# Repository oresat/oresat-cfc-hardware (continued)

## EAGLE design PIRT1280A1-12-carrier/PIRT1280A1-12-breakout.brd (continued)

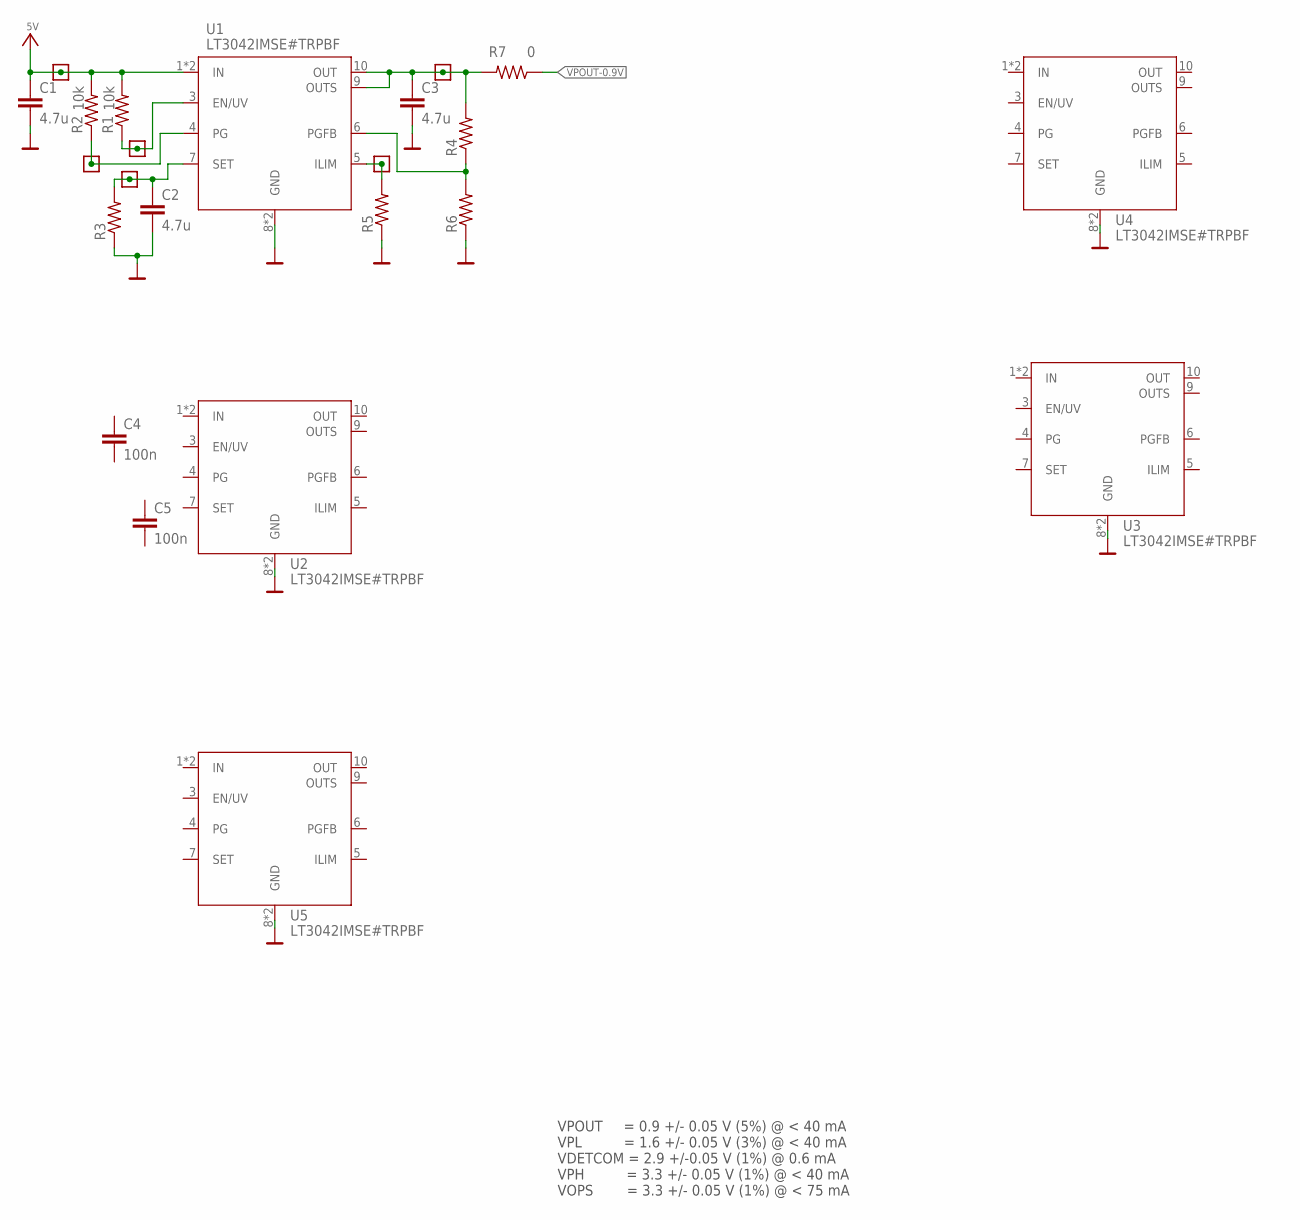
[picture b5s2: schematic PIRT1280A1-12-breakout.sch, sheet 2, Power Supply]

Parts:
C1, C2, C3: 4.7u; .0603-C-NOSILK
C4, C5: 100n; .0603-C-NOSILK
R1, R2: 10k; .0603-C-NOSILK
R3, R4, R5, R6: R-US_0603-C-NOSILK; .0603-C-NOSILK
R7: 0; .0603-C-NOSILK
TP1, TP10, TP11, TP12, TP13, TP14: TEST-POINT-LARGE-SQUARE; 1X01
U1, U2, U3, U4, U5: LT3042IMSE#TRPBF; SOP50P490X110-11N

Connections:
5V: C1.1, R1.2, R2.2, TP12.1, U1.1 (IN), U1.2 (IN)
GND: C1.2, C2.2, C3.2, R3.1, R5.1, R6.1, U1.8 (GND), U1.11 (GND), U2.8 (GND), U2.11 (GND), U3.8 (GND), U3.11 (GND), U4.8 (GND), U4.11 (GND), U5.8 (GND), U5.11 (GND); also elsewhere on the board
IN: U2.1 (IN), U2.2 (IN), U3.1 (IN), U3.2 (IN), U4.1 (IN), U4.2 (IN), U5.1 (IN), U5.2 (IN)
unnamed: R1.1, TP11.1, U1.3 (EN/UV)
unnamed: C2.1, R3.2, TP1.1, U1.7 (SET)
unnamed: R2.1, TP10.1, U1.4 (PG)
unnamed: R5.2, TP14.1, U1.5 (ILIM)
unnamed: R4.1, R6.2, U1.6 (PGFB)
OUT: U2.10 (OUT), U3.10 (OUT), U4.10 (OUT), U5.10 (OUT)
OUTS: U2.9 (OUTS), U3.9 (OUTS), U4.9 (OUTS), U5.9 (OUTS)
VPOUT: C3.1, R4.2, R7.2, TP13.1, U1.9 (OUTS), U1.10 (OUT)
VPOUT-0.9V: R7.1; also elsewhere on the board

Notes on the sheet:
VPOUT = 0.9 +/- 0.05 V (5%) @ < 40 mA VPL = 1.6 +/- 0.05 V (3%) @ < 40 mA VDETCOM = 2.9 +/-0.05 V (1%) @ 0.6 mA VPH = 3.3 +/- 0.05 V (1%) @ < 40 mA VOPS = 3.3 +/- 0.05 V (1%) @ < 75 mA

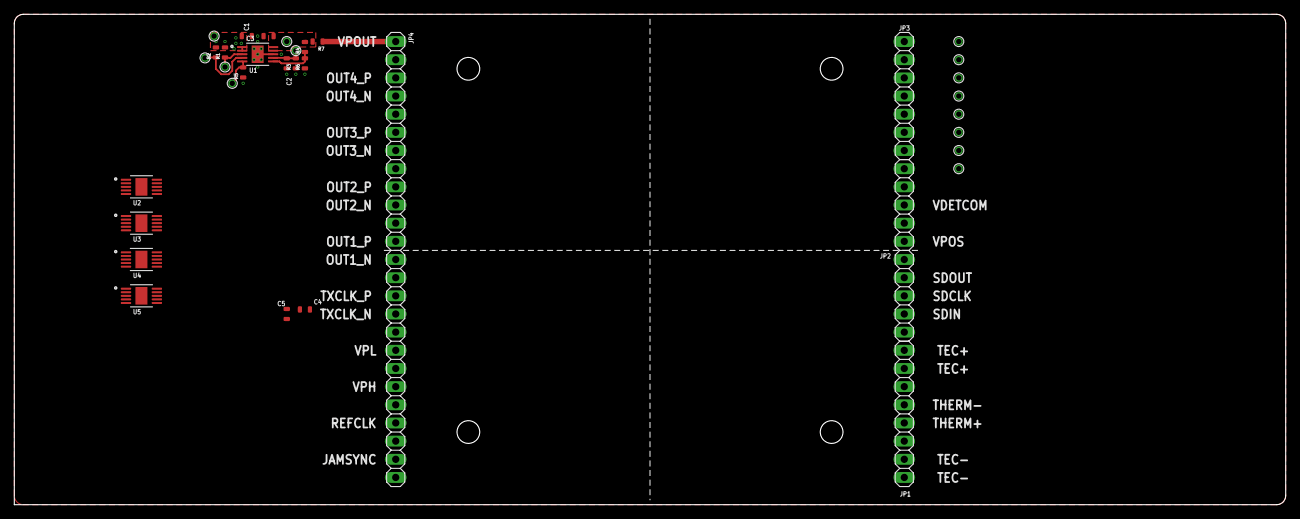
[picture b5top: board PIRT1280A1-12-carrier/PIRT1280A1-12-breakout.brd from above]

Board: 4 copper layers, 177.8 x 68.6 mm, 35 parts (0 on the bottom side), 22 nets.

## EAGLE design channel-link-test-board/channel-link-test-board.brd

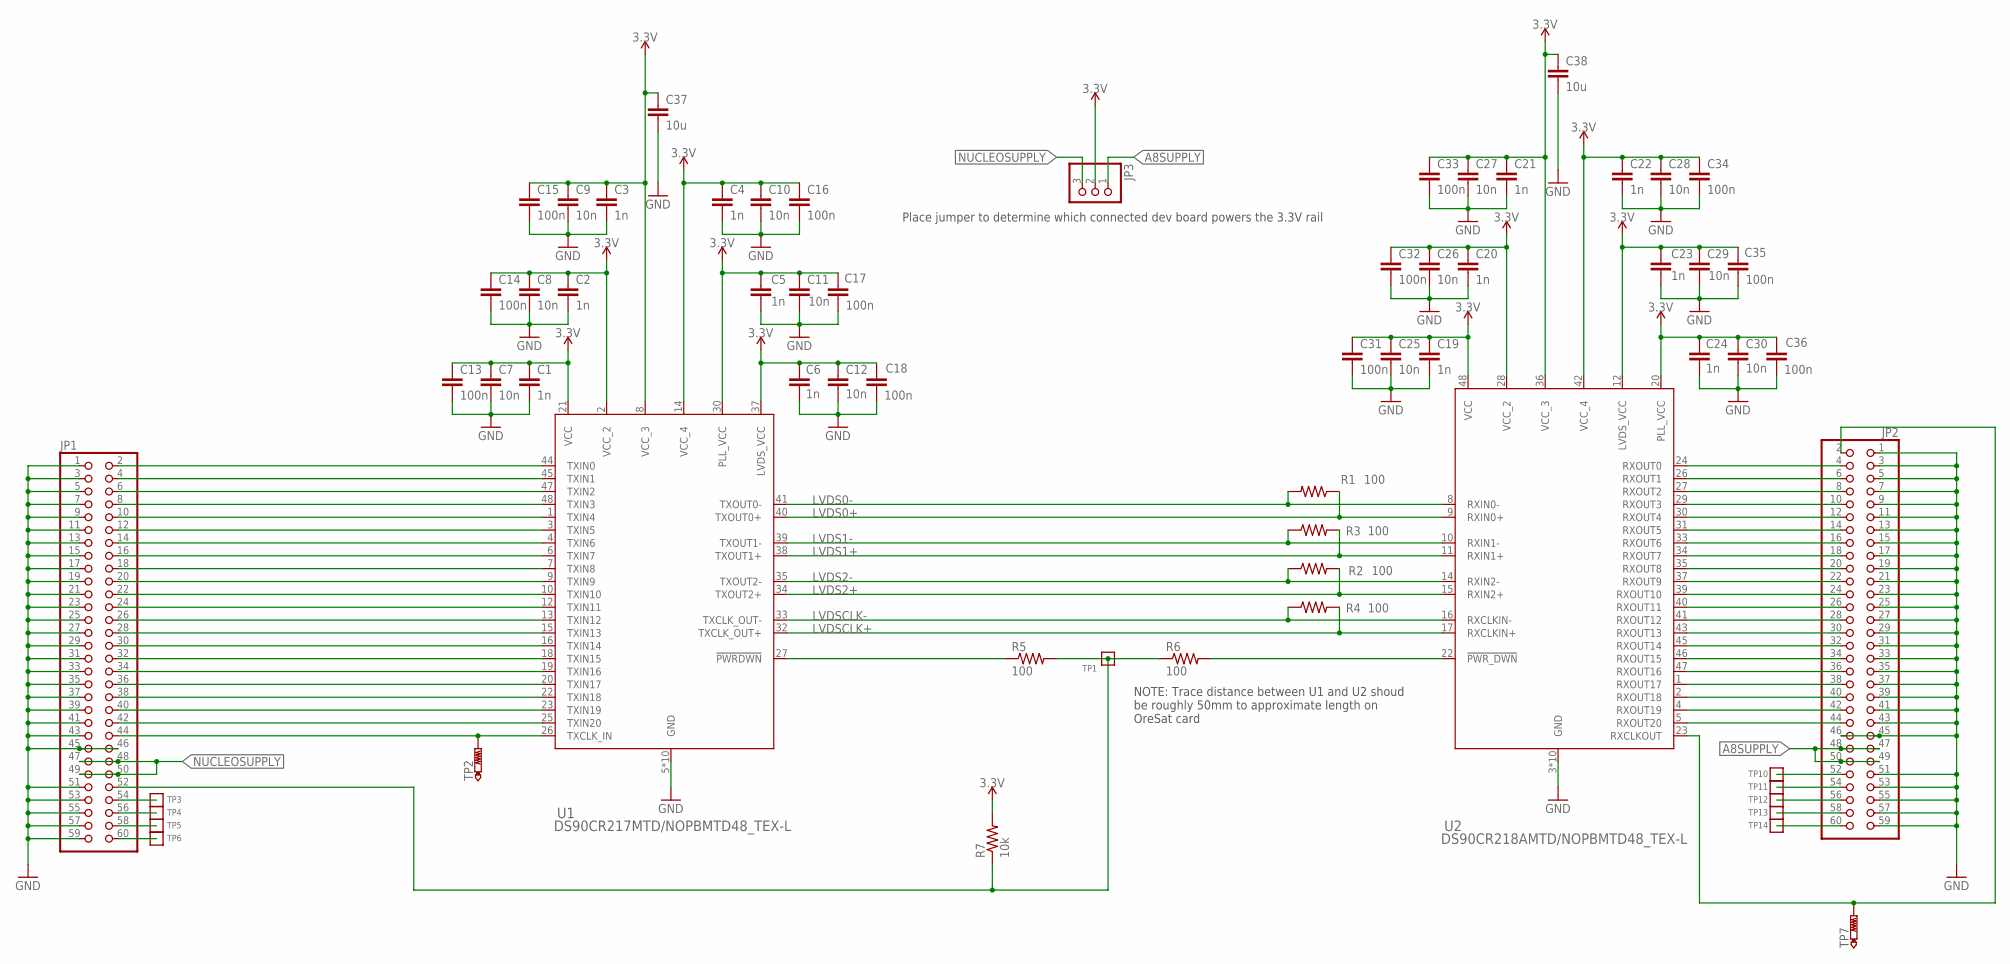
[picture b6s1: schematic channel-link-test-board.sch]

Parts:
C1, C2, C3, C4, C5, C6, C19, C20, C21, C22, C23, C24: 1n; .0402-C-NOSILK; MPN GRM155R71H102KA01J
C7, C8, C9, C10, C11, C26, C27, C28, C29, C30: 10n; .0603-C-NOSILK; MPN C0603C103M5RACTU
C12, C25: 10n; .0402-C-NOSILK; MPN C0603C103M5RACTU
C13, C15, C16, C17, C18, C32, C33, C34, C35, C36: 100n; .0805-C-NOSILK; MPN C0805C104Z5VACTU
C14, C31: 100n; .0402-C-NOSILK; MPN C0805C104Z5VACTU
C37, C38: 10u; .0603-C-NOSILK; MPN GRM188R61A106KE69J
JP1, JP2: PINHD-2X30; 2X30; MPN 71918-160LF
JP3: PINHD-1X3; 1X03; MPN 61300311121
R1, R2, R3, R4: 100; .0201-C-NOSILK; MPN RC0201FR-07100RL
R5, R6: 100; .0603-C-NOSILK; MPN RC0603FR-07100RL
R7: 10k; .0603-C-NOSILK; MPN RC0603FR-0710KL
TP1, TP3, TP4, TP5, TP6, TP10, TP11, TP12, TP13, TP14: TEST-POINT-LARGE-SQUARE; 1X01
TP2, TP7: PTR1B2,54; B2,54
U1: DS90CR217MTD/NOPBMTD48_TEX-L; MTD48_TEX-L
U2: DS90CR218AMTD/NOPBMTD48_TEX-L; MTD48_TEX-L

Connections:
3.3V: C1.1, C2.1, C3.1, C4.1, C5.1, C6.1, C7.1, C8.1, C9.1, C10.1, C11.1, C12.1, C13.1, C14.1, C15.1, C16.1, C17.1, C18.1, C19.1, C20.1, C21.1, C22.1, C23.1, C24.1, C25.1, C26.1, C27.1, C28.1, C29.1, C30.1, C31.1, C32.1, C33.1, C34.1, C35.1, C36.1, C37.1, C38.1, JP3.2, R7.2, U1.2 (VCC_2), U1.8 (VCC_3), U1.14 (VCC_4), U1.21 (VCC), U1.30 (PLL_VCC), U1.37 (LVDS_VCC), U2.12 (LVDS_VCC), U2.20 (PLL_VCC), U2.28 (VCC_2), U2.36 (VCC_3), U2.42 (VCC_4), U2.48 (VCC)
A8SUPPLY: JP2.47, JP2.48, JP2.49, JP2.50, JP3.1
GND: C1.2, C2.2, C3.2, C4.2, C5.2, C6.2, C7.2, C8.2, C9.2, C10.2, C11.2, C12.2, C13.2, C14.2, C15.2, C16.2, C17.2, C18.2, C19.2, C20.2, C21.2, C22.2, C23.2, C24.2, C25.2, C26.2, C27.2, C28.2, C29.2, C30.2, C31.2, C32.2, C33.2, C34.2, C35.2, C36.2, C37.2, C38.2, JP1.1, JP1.3, JP1.5, JP1.7, JP1.9, JP1.11, JP1.13, JP1.15, JP1.17, JP1.19, JP1.21, JP1.23, JP1.25, JP1.27, JP1.29, JP1.31, JP1.33, JP1.35, JP1.37, JP1.39, JP1.41, JP1.43, JP1.45, JP1.46, JP1.51, JP1.53, JP1.55, JP1.57, JP1.59, JP2.1, JP2.3, JP2.5, JP2.7, JP2.9, JP2.11, JP2.13, JP2.15, JP2.17, JP2.19, JP2.21, JP2.23, JP2.25, JP2.27, JP2.29, JP2.31, JP2.33, JP2.35, JP2.37, JP2.39, JP2.41, JP2.43, JP2.45, JP2.46, JP2.51, JP2.53, JP2.55, JP2.57, JP2.59, U1.5 (GND), U1.11 (GND), U1.17 (GND), U1.24 (GND), U1.28 (GND), U1.29 (GND), U1.31 (GND), U1.36 (GND), U1.42 (GND), U1.46 (GND), U2.3 (GND), U2.7 (GND), U2.13 (GND), U2.18 (GND), U2.19 (GND), U2.21 (GND), U2.25 (GND), U2.32 (GND), U2.38 (GND), U2.44 (GND)
LVDS0+: R1.1, U1.40 (TXOUT0+), U2.9 (RXIN0+)
LVDS0-: R1.2, U1.41 (TXOUT0-), U2.8 (RXIN0-)
LVDS1+: R3.2, U1.38 (TXOUT1+), U2.11 (RXIN1+)
LVDS1-: R3.1, U1.39 (TXOUT1-), U2.10 (RXIN1-)
LVDS2+: R2.2, U1.34 (TXOUT2+), U2.15 (RXIN2+)
LVDS2-: R2.1, U1.35 (TXOUT2-), U2.14 (RXIN2-)
LVDSCLK+: R4.2, U1.32 (TXCLK_OUT+), U2.17 (RXCLKIN+)
LVDSCLK-: R4.1, U1.33 (TXCLK_OUT-), U2.16 (RXCLKIN-)
unnamed: JP1.2, U1.44 (TXIN0)
unnamed: JP1.4, U1.45 (TXIN1)
unnamed: JP1.6, U1.47 (TXIN2)
unnamed: JP1.8, U1.48 (TXIN3)
unnamed: JP1.10, U1.1 (TXIN4)
unnamed: JP1.12, U1.3 (TXIN5)
unnamed: JP1.14, U1.4 (TXIN6)
unnamed: JP1.16, U1.6 (TXIN7)
unnamed: JP1.18, U1.7 (TXIN8)
unnamed: JP1.20, U1.9 (TXIN9)
unnamed: JP1.22, U1.10 (TXIN10)
unnamed: JP1.24, U1.12 (TXIN11)
unnamed: JP1.26, U1.13 (TXIN12)
unnamed: JP1.28, U1.15 (TXIN13)
unnamed: JP1.30, U1.16 (TXIN14)
unnamed: JP1.32, U1.18 (TXIN15)
unnamed: JP1.34, U1.19 (TXIN16)
unnamed: JP1.36, U1.20 (TXIN17)
unnamed: JP1.38, U1.22 (TXIN18)
unnamed: JP1.40, U1.23 (TXIN19)
unnamed: JP1.42, U1.25 (TXIN20)
unnamed: JP1.44, TP2.TP, U1.26 (TXCLK_IN)
unnamed: JP2.4, U2.24 (RXOUT0)
unnamed: JP2.6, U2.26 (RXOUT1)
unnamed: R5.1, U1.27 (!PWRDWN)
unnamed: R6.2, U2.22 (!PWR_DWN)
unnamed: JP2.8, U2.27 (RXOUT2)
unnamed: JP2.10, U2.29 (RXOUT3)
unnamed: JP2.12, U2.30 (RXOUT4)
unnamed: JP2.14, U2.31 (RXOUT5)
unnamed: JP2.16, U2.33 (RXOUT6)
unnamed: JP2.18, U2.34 (RXOUT7)
unnamed: JP2.20, U2.35 (RXOUT8)
unnamed: JP2.22, U2.37 (RXOUT9)
unnamed: JP2.24, U2.39 (RXOUT10)
unnamed: JP2.26, U2.40 (RXOUT11)
unnamed: JP2.28, U2.41 (RXOUT12)
unnamed: JP2.52, TP10.1
unnamed: JP2.54, TP11.1
unnamed: JP2.56, TP12.1
unnamed: JP2.58, TP13.1
unnamed: JP2.60, TP14.1
unnamed: JP2.30, U2.43 (RXOUT13)
unnamed: JP2.32, U2.45 (RXOUT14)
unnamed: JP2.34, U2.46 (RXOUT15)
unnamed: JP2.36, U2.47 (RXOUT16)
unnamed: JP1.52, R5.2, R6.1, R7.1, TP1.1
unnamed: JP1.54, TP3.1
unnamed: JP1.56, TP4.1
unnamed: JP1.58, TP5.1
unnamed: JP1.60, TP6.1
unnamed: JP2.38, U2.1 (RXOUT17)
unnamed: JP2.40, U2.2 (RXOUT18)
unnamed: JP2.42, U2.4 (RXOUT19)
unnamed: JP2.44, U2.5 (RXOUT20)
unnamed: JP2.2, TP7.TP, U2.23 (RXCLKOUT)
NUCLEOSUPPLY: JP1.47, JP1.48, JP1.49, JP1.50, JP3.3

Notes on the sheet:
NOTE: Trace distance between U1 and U2 shoud be roughly 50mm to approximate length on OreSat card
Place jumper to determine which connected dev board powers the 3.3V rail

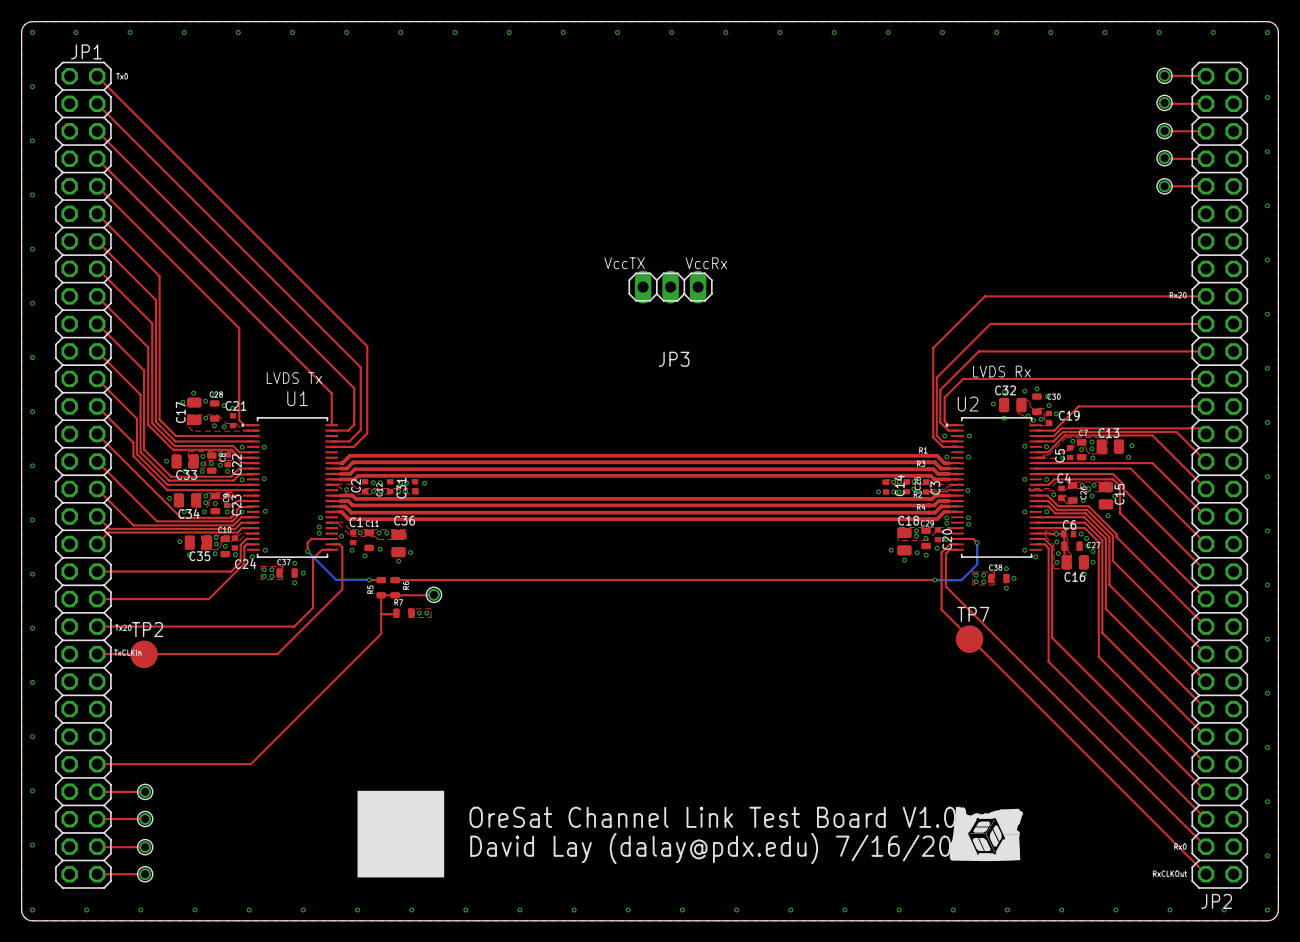
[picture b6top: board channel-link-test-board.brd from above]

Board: 4 copper layers, 116.0 x 83.0 mm, 62 parts (0 on the bottom side), 68 nets.

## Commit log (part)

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2020-07-16 first go around on the channel link test board
2020-07-17 minor cleanup, ground stitching, attributes
2020-07-19 moved LVDS lines so I could bypass the LVDS VCC
2020-07-20 ocd fixes
2020-07-20 Some minor DRCs.
2020-07-20 ROUND corners are BEST CORNERS.
2020-07-22 updated attributes and BOM
2021-01-18 Library file for the PIRT1280A1-12 camera.
2021-01-18 First pass at the PIRT breakout board.
2021-01-21 Mods from Oliver and Scott; more testpoints, stitching, ground points.
2021-01-26 Prototype of PIRT sensor and an example LT3042 power supply layout for one of the supplies.
2021-04-06 mostly finished PIRT breakout
2021-04-12 mostly finished with PIRT1280 carrier
2021-04-12 touch ups
2021-04-12 pre-review cleanup
2021-04-13 address review comments
2021-05-10 added PIRT1280 BOM, used internal library in carrier, added attributes
2021-05-10 Fixed BOM (a lot of wrong packages, no mfr, no descriptions, wrong formatting). Fixed 16 MHz crystal attributes.
2021-07-15 started cFC card
2021-07-20 rebase: backup work
2021-07-22 Add initial design for cfc emulator card
2021-07-22 Fix up ERC warnings
2021-07-23 Tweak up diff pairs and remove gerbers
2021-07-28 mostly finished sensor card
2021-08-01 mostly finished octavo card
2021-08-01 oh god almost done
2021-08-01 couple more changes
2021-08-01 remove todo
2021-08-02 boards finished
2021-08-02 update attrs
2021-08-02 xml change
2021-08-02 fixed resistor array value
2021-08-18 Fixed R27 attributes, and fixed names layer
2021-08-18 Added CFC sensor card BOM
2021-08-20 update attributes
2021-08-20 Updated OPD address resistors, LED resistors (AAAAAUGH MY EYES), and OPD shunt resistor to give the CFC sensor card addrss 0x1E and a 2.95 A current limit.
2021-08-24 Fix ~powerdown handling to add GPIO control from Icebreaker. Add pullup on ~powerdown to default it to powered up. Fix footprint error on TX chip (two pins swapped). Fix pin swap error on both LVDS p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
2022-11-08 Revamp the CFC hardware repo to keep v1 (giant copper block version) and start v2 (radiator version).
2022-11-08 OCD renaming
2022-11-08 New KiCAD project, schematic, and PCB layout for v2 of the CFC Sensor Board. Note that the schematic is empty, but the board reflects the 2022-09-15 sensor card outline from OnShape.
2022-11-08 Adding PIRT sensor. Needs a double check, and the rest of the symbol.
2022-11-09 Make sensor card thermal strap fastener passthroughts 5 mm so we can use a 4.5 mm washer.
2022-11-22 Add new DXF with bottom layer keepouts from the lens mount, and add it to the user.documentation layer.
2023-01-21 feat: cfc sensor card v2
2023-01-25 Changes from board fab: fixed card outline center hole (no fill), excluded some new violations, changed minimum mask web to 0.
2023-02-13 Generated ibom
2023-02-20 added OPD address resistors
2023-02-20 OPD CB shunt resistor is 10m, not 100m. Cleanup documentation. Also clean up documentation on other pages.
2023-05-12 Added CFC minibackplane requirements and drawing.
2023-05-13 Added note to Ben about a Ben Idea.
2023-05-14 Created a first revision of the mini backplane
2023-05-14 Updated 3d models
2023-05-14 Cleaned up schematic and silkscreen
2023-05-14 Switched to 2 layers
2023-05-14 Fixed silkscreen
2023-05-18 Updated outline DXF
2023-05-21 Updated board based on CFC meeting
2023-05-28 Made screws bigger and moved stuff
2023-05-28 Updated BOM
2023-06-01 Added formatted BOM for the minibackplane, including board connectors.
2023-06-19 Added not on Trinket wiring bug.
2023-07-16 Fixed wrong NPs in CFC sensor card OPD. Updated to KiCAD 7.
2023-07-26 Added TEC softstart LTspice simulation
2023-08-04 Added soft start to sensor card and cleaned up some KiCad warnings
2024-02-01 Add scripts subdirectory for test scripts for sensor. Add plothisto.py which plots histograms for the raw sensor pixel data
2025-06-12 Initial conversion of cfc processor board from Eagle to KiCAD 9
    Still using converted Eagle symbols and footprints.
2025-08-28 Clean up CFC Processor Card from Scott's initial import which was Gerber identical to origianl EAGLE schematic. Interestingly, this version was already changed for the v2 backplane which is great. Al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
2025-08-30 Big cleanup - fixed a billion ERCs and DRCs. Switched a bunch of parts over to OreSat parts. Added analog switch on UART so CFC processor can talk serial to C3. Last thing left: clean up passives wit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
2025-08-31 more trace polishing.
2025-08-31 More layout polishing Removed unused SPI EEPROM.
2025-09-13 Big sweep through to clean up from v2.0 to v2.1 board. Cleaned up all of the Github issues, and even added a MPS2410A CC driver to run the TEC for increased efficiency. Left old switch on board just 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
2025-09-13 renamed files to standard filenames, removed html file.
2025-09-13 Updated the README, finally
2025-09-13 Added a few pictures and cleaned up readme
2025-09-13 Links to pictures)
2025-09-13 adding license
2025-09-13 Final polish on README
2025-09-14 Final polish on schematic and PCB. Cleaned up BOM, fixed github issues which were not really issues. Lots of BOM cleanup, with MPNs and DPNs.
2025-09-14 Fix and complete BOM, fix lots of little layout issue and footprint inconsistancies, and polish. Ready to go!
2025-09-15 Changed mfg date, more stitching and layout tweaking.
2025-09-15 Updated mfg date. More stiching. More layout tweaking. Done.
2025-09-15 Rename old processor board since it's old and don't want people going there. Eventually, we'll remove, but those cards are still in use so worth it to have both for right now.
2025-09-15 Some minor cleanup on TEC schematic, no change to board
2025-09-15 File naming cleanup because OCD
2025-09-15 Final renaming!
2025-09-15 Fixed up crappy symbol on OPD; no change to layout, just schematic and link to PCB.
2026-06-23 Schematic Changes
    Made schematic into hierarchy view. Revised OPD to match modern OPD. Removed connectors page. Separated power sequencing and PIRT sensor into 2 pages.
2026-06-24 CFC processor schematic Change
    changed to hierarchy view, changed all global net labels to hierarchy labels, changed all resistor, capacitor, and ground symbols to modern oresat labels. Deleted connectors sheet and added .history 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
2026-06-24 Updated OPD
    couple of resistors and caps added to schematic. Changed USB ESD clamp VDD to 3.3v instead of octavo created VDD line.
2026-06-25 Update
    Added pull down resistors and removed therm + and sensor enable and added i2c support for cfc sensor card.
2026-06-27 Update
    Fixed a couple of library issues on testpoints and other misc components. Added Pull up resistors to 8 channel i2c ic
2026-06-28 Update
    Changed passive component footprints to 0603 no silk c. Fixed OPD UART termination resistor on cfc processor card. Added low temp co and tolerance resistor for NTC thermistor tec voltage divider.
2026-06-28 Update
    Cleaned up library preferences, added voltage controlled constant current note. Added RC filter to therm+ measurement made against the 2.5vref.
2026-06-30 Update
    Added bidirectional TEC control with DRV8212 IC. Added Sensor enable pin back to processor; in case of i2c hang up octavo can still disable sensor.
2026-06-30 update
    Changed a couple of test points on OPD to through hole test points. Added tables to DRV8212 on sensor schematic+ other visual improvements to processor schematic.
